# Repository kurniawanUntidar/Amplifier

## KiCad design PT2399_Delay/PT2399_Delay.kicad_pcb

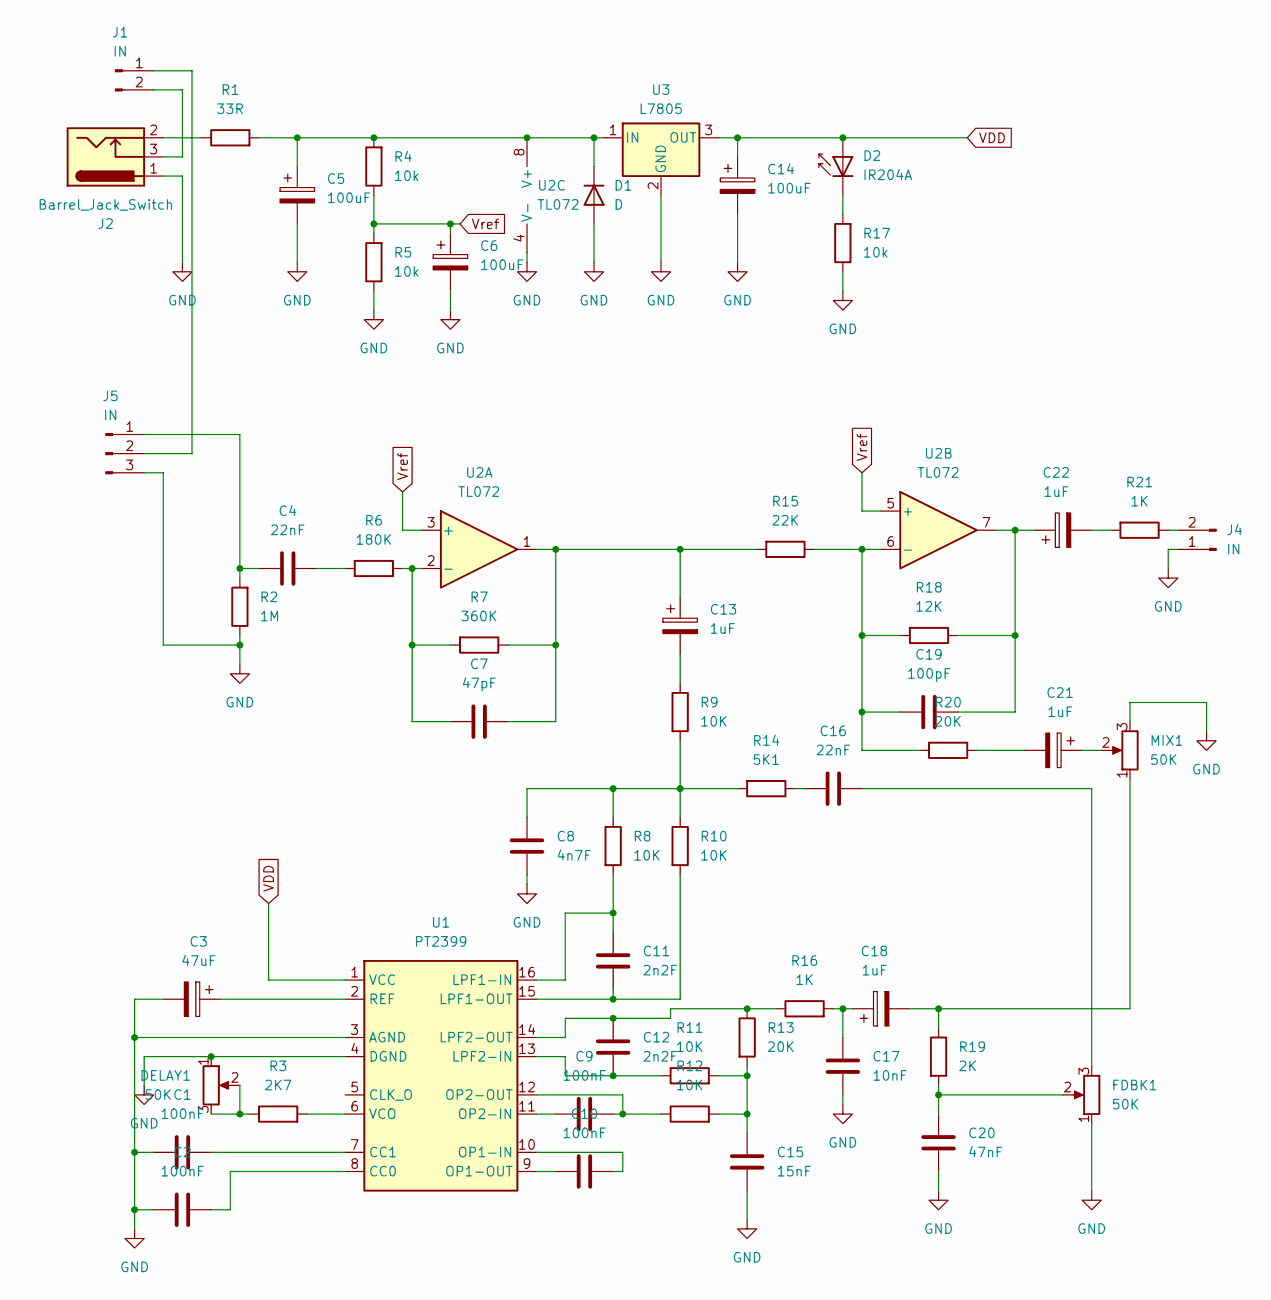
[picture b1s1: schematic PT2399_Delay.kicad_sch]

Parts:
C1, C2, C9, C10: 100nF; C_Axial_L3.8mm_D2.6mm_P7.50mm_Horizontal
C3: 47uF; CP_Radial_D4.0mm_P2.00mm
C4, C16: 22nF; C_Axial_L3.8mm_D2.6mm_P7.50mm_Horizontal
C5, C6, C14: 100uF; CP_Radial_D5.0mm_P2.50mm
C7: 47pF; C_Axial_L3.8mm_D2.6mm_P7.50mm_Horizontal
C8: 4n7F; C_Axial_L3.8mm_D2.6mm_P7.50mm_Horizontal
C11, C12: 2n2F; C_Axial_L3.8mm_D2.6mm_P7.50mm_Horizontal
C13, C18, C21, C22: 1uF; CP_Radial_D4.0mm_P2.00mm
C15: 15nF; C_Axial_L3.8mm_D2.6mm_P7.50mm_Horizontal
C17: 10nF; C_Axial_L3.8mm_D2.6mm_P7.50mm_Horizontal
C19: 100pF; C_Axial_L3.8mm_D2.6mm_P7.50mm_Horizontal
C20: 47nF; C_Axial_L3.8mm_D2.6mm_P7.50mm_Horizontal
D1: D; D_SMC-RM10_Universal_Handsoldering
D2: IR204A; LED_D3.0mm_IRBlack
DELAY1: 50K; Potentiometer_Omeg_PC16BU_Vertical
FDBK1: 50K; Potentiometer_Omeg_PC16BU_Vertical
J1, J4: IN; JST_XA_B02B-XASK-1_1x02_P2.50mm_Vertical
J2: Barrel_Jack_Switch; BarrelJack_GCT_DCJ200-10-A_Horizontal
J5: IN; JST_XA_B03B-XASK-1-A_1x03_P2.50mm_Vertical
MIX1: 50K; Potentiometer_Omeg_PC16BU_Vertical
R1: 33R; R_Axial_DIN0204_L3.6mm_D1.6mm_P5.08mm_Horizontal
R2: 1M; R_Axial_DIN0204_L3.6mm_D1.6mm_P5.08mm_Horizontal
R3: 2K7; R_Axial_DIN0204_L3.6mm_D1.6mm_P5.08mm_Horizontal
R4, R5, R17: 10k; R_Axial_DIN0204_L3.6mm_D1.6mm_P5.08mm_Horizontal
R6: 180K; R_Axial_DIN0204_L3.6mm_D1.6mm_P5.08mm_Horizontal
R7: 360K; R_Axial_DIN0204_L3.6mm_D1.6mm_P5.08mm_Horizontal
R8, R9, R10, R11, R12: 10K; R_Axial_DIN0204_L3.6mm_D1.6mm_P5.08mm_Horizontal
R13, R20: 20K; R_Axial_DIN0204_L3.6mm_D1.6mm_P5.08mm_Horizontal
R14: 5K1; R_Axial_DIN0204_L3.6mm_D1.6mm_P5.08mm_Horizontal
R15: 22K; R_Axial_DIN0204_L3.6mm_D1.6mm_P5.08mm_Horizontal
R16, R21: 1K; R_Axial_DIN0204_L3.6mm_D1.6mm_P5.08mm_Horizontal
R18: 12K; R_Axial_DIN0204_L3.6mm_D1.6mm_P5.08mm_Horizontal
R19: 2K; R_Axial_DIN0204_L3.6mm_D1.6mm_P5.08mm_Horizontal
U1: PT2399; DIP-16_W7.62mm
U2: TL072; DIP-8_W7.62mm
U3: L7805; TO-220F-3_Horizontal_TabUp

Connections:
GND: C1.2, C2.2, C3.2, C5.2, C6.2, C8.1, C14.2, C15.1, C17.1, C20.1, D1.2 (A), DELAY1.1, FDBK1.1, J2.1, J4.1, J5.3, MIX1.3, R2.1, R5.1, R17.1, U1.3 (AGND), U1.4 (DGND), U2.4 (V-), U3.2 (GND)
unnamed: C4.2, R6.2
unnamed: C8.2, R8.1, R9.2, R10.1, R14.2
unnamed: C7.2, C13.1, R7.1, R15.2, U2.1
unnamed: C13.2, R9.1
unnamed: C15.2, R11.2, R12.2, R13.2
unnamed: C16.1, FDBK1.3
unnamed: C16.2, R14.1
unnamed: C17.2, C18.1, R16.2
unnamed: C18.2, MIX1.1, R19.1
unnamed: C19.2, C22.1, R18.1, U2.7
unnamed: C20.2, FDBK1.2, R19.2
unnamed: C21.1, MIX1.2
unnamed: C21.2, R20.1
unnamed: C22.2, R21.2
unnamed: C5.1, D1.1 (K), R1.2, R4.2, U2.8 (V+), U3.1 (IN)
unnamed: D2.1 (K), R17.2
unnamed: DELAY1.2, DELAY1.3, R3.1
unnamed: J1.1, J5.2
unnamed: J1.2, J2.3
unnamed: J2.2, R1.1
unnamed: J4.2, R21.1
unnamed: C4.1, J5.1, R2.2
unnamed: C2.1, U1.8 (CC0)
unnamed: C1.1, U1.7 (CC1)
unnamed: C11.2, R8.2, U1.16 (LPF1-IN)
unnamed: C11.1, R10.2, U1.15 (LPF1-OUT)
unnamed: C12.1, R11.1, U1.13 (LPF2-IN)
unnamed: C12.2, R13.1, R16.1, U1.14 (LPF2-OUT)
unnamed: C10.1, U1.10 (OP1-IN)
unnamed: C10.2, U1.9 (OP1-OUT)
unnamed: C9.2, U1.11 (OP2-IN)
unnamed: C9.1, R12.1, U1.12 (OP2-OUT)
unnamed: C3.1, U1.2 (REF)
unnamed: R3.2, U1.6 (VCO)
unnamed: C7.1, R6.1, R7.2, U2.2 (-)
unnamed: C19.1, R15.1, R18.2, R20.2, U2.6 (-)
VDD: C14.1, D2.2 (A), U1.1 (VCC), U3.3 (OUT)
Vref: C6.1, R4.1, R5.2, U2.3 (+), U2.5 (+)

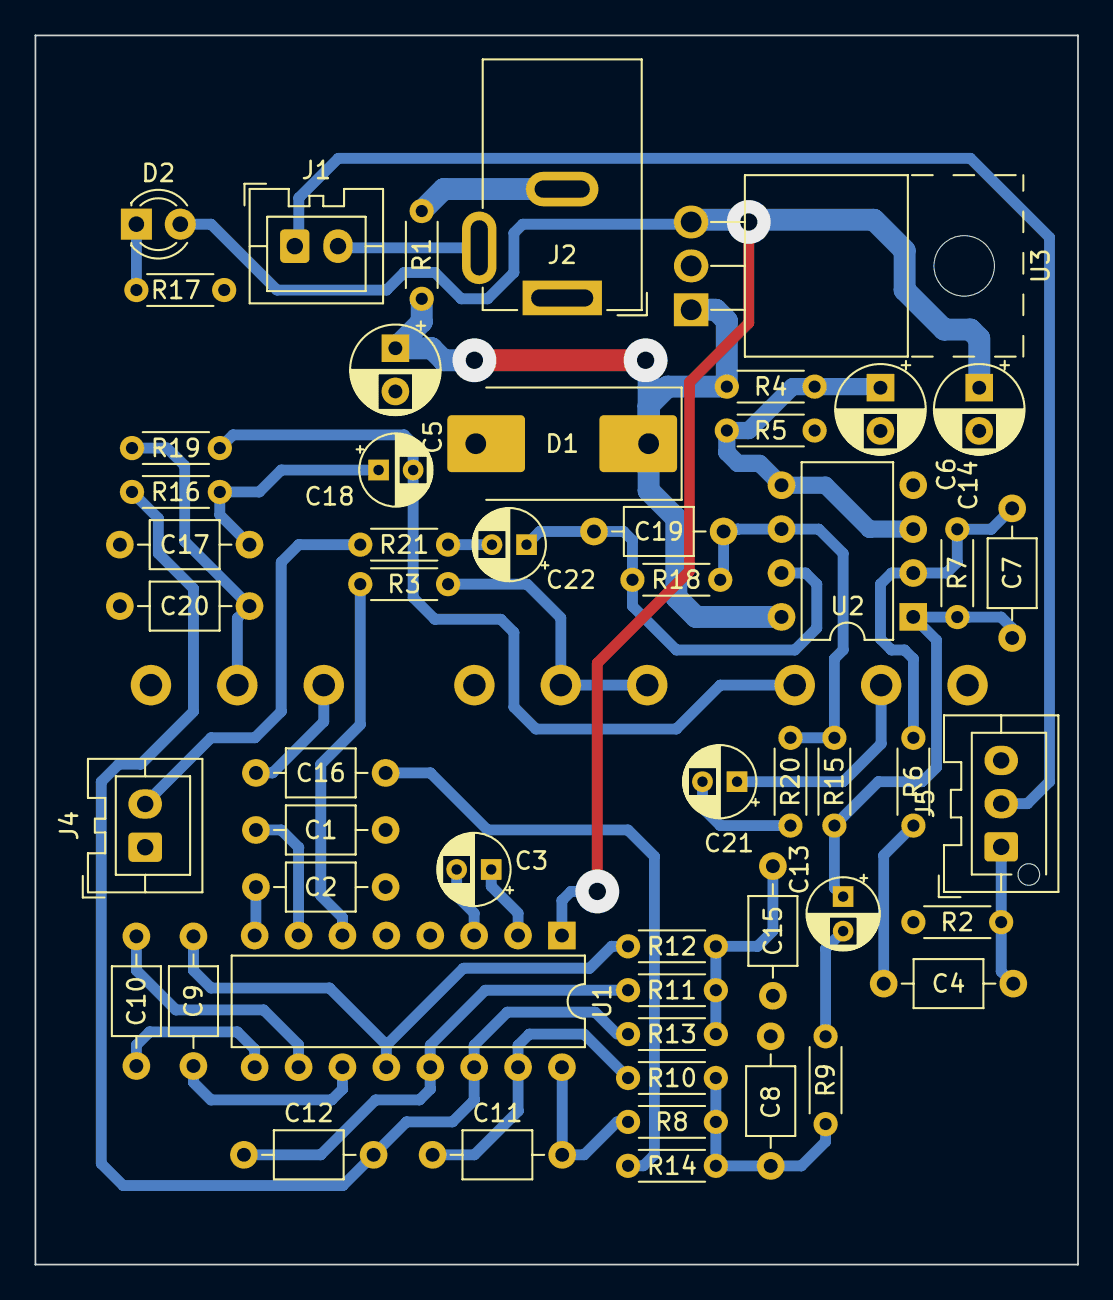
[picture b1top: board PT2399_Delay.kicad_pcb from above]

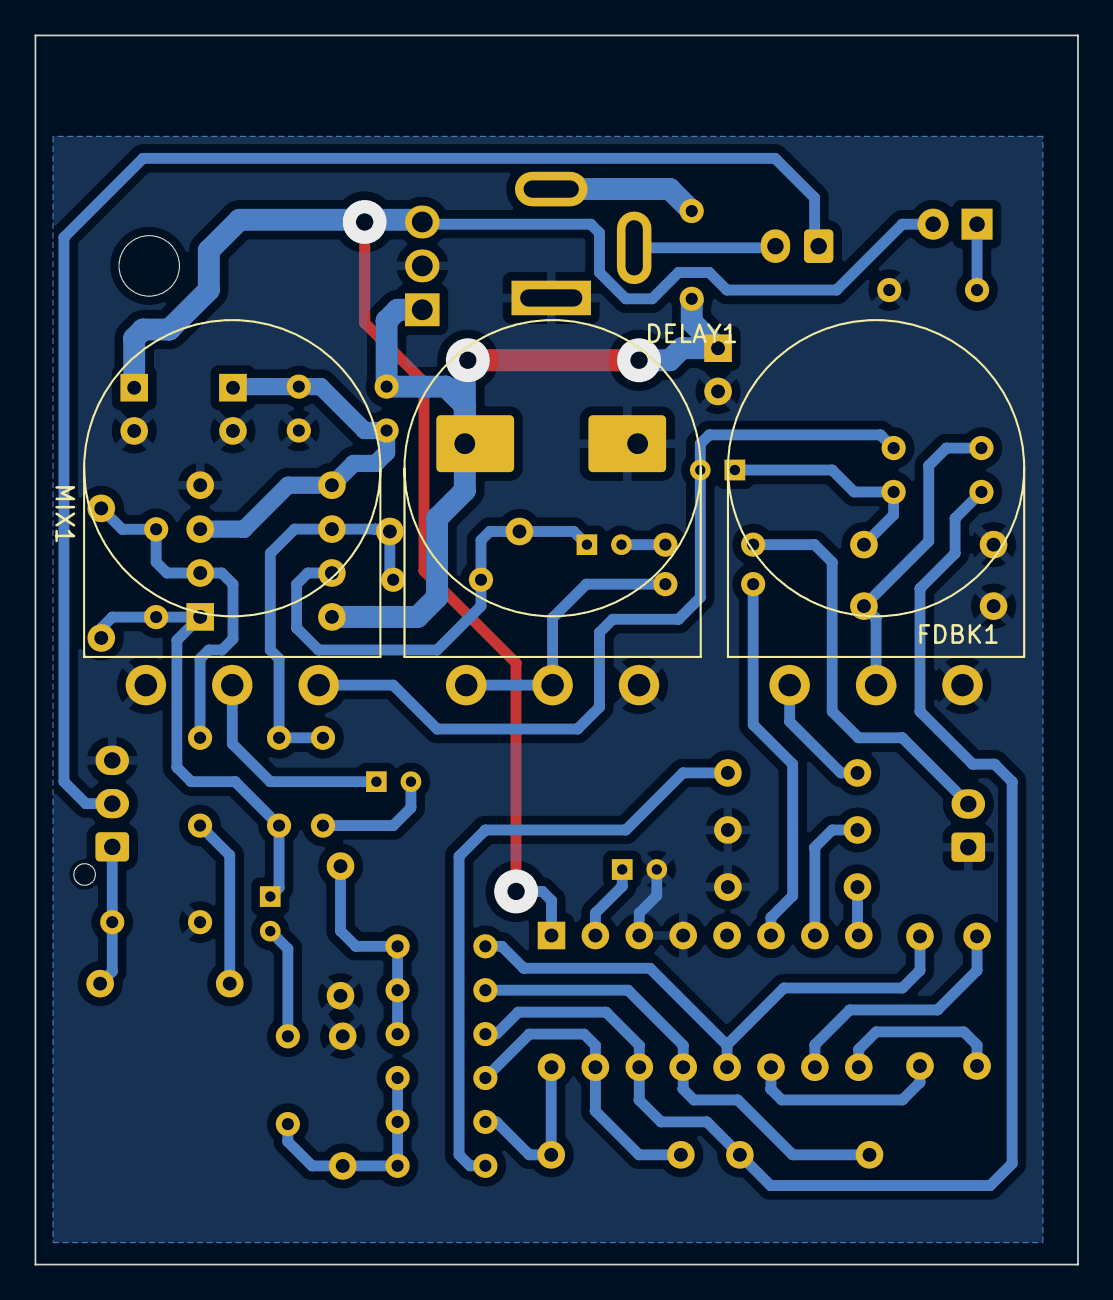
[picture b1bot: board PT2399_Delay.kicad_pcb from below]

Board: 2 copper layers, 60.3 x 71.1 mm, 55 parts (3 on the bottom side), 39 nets.

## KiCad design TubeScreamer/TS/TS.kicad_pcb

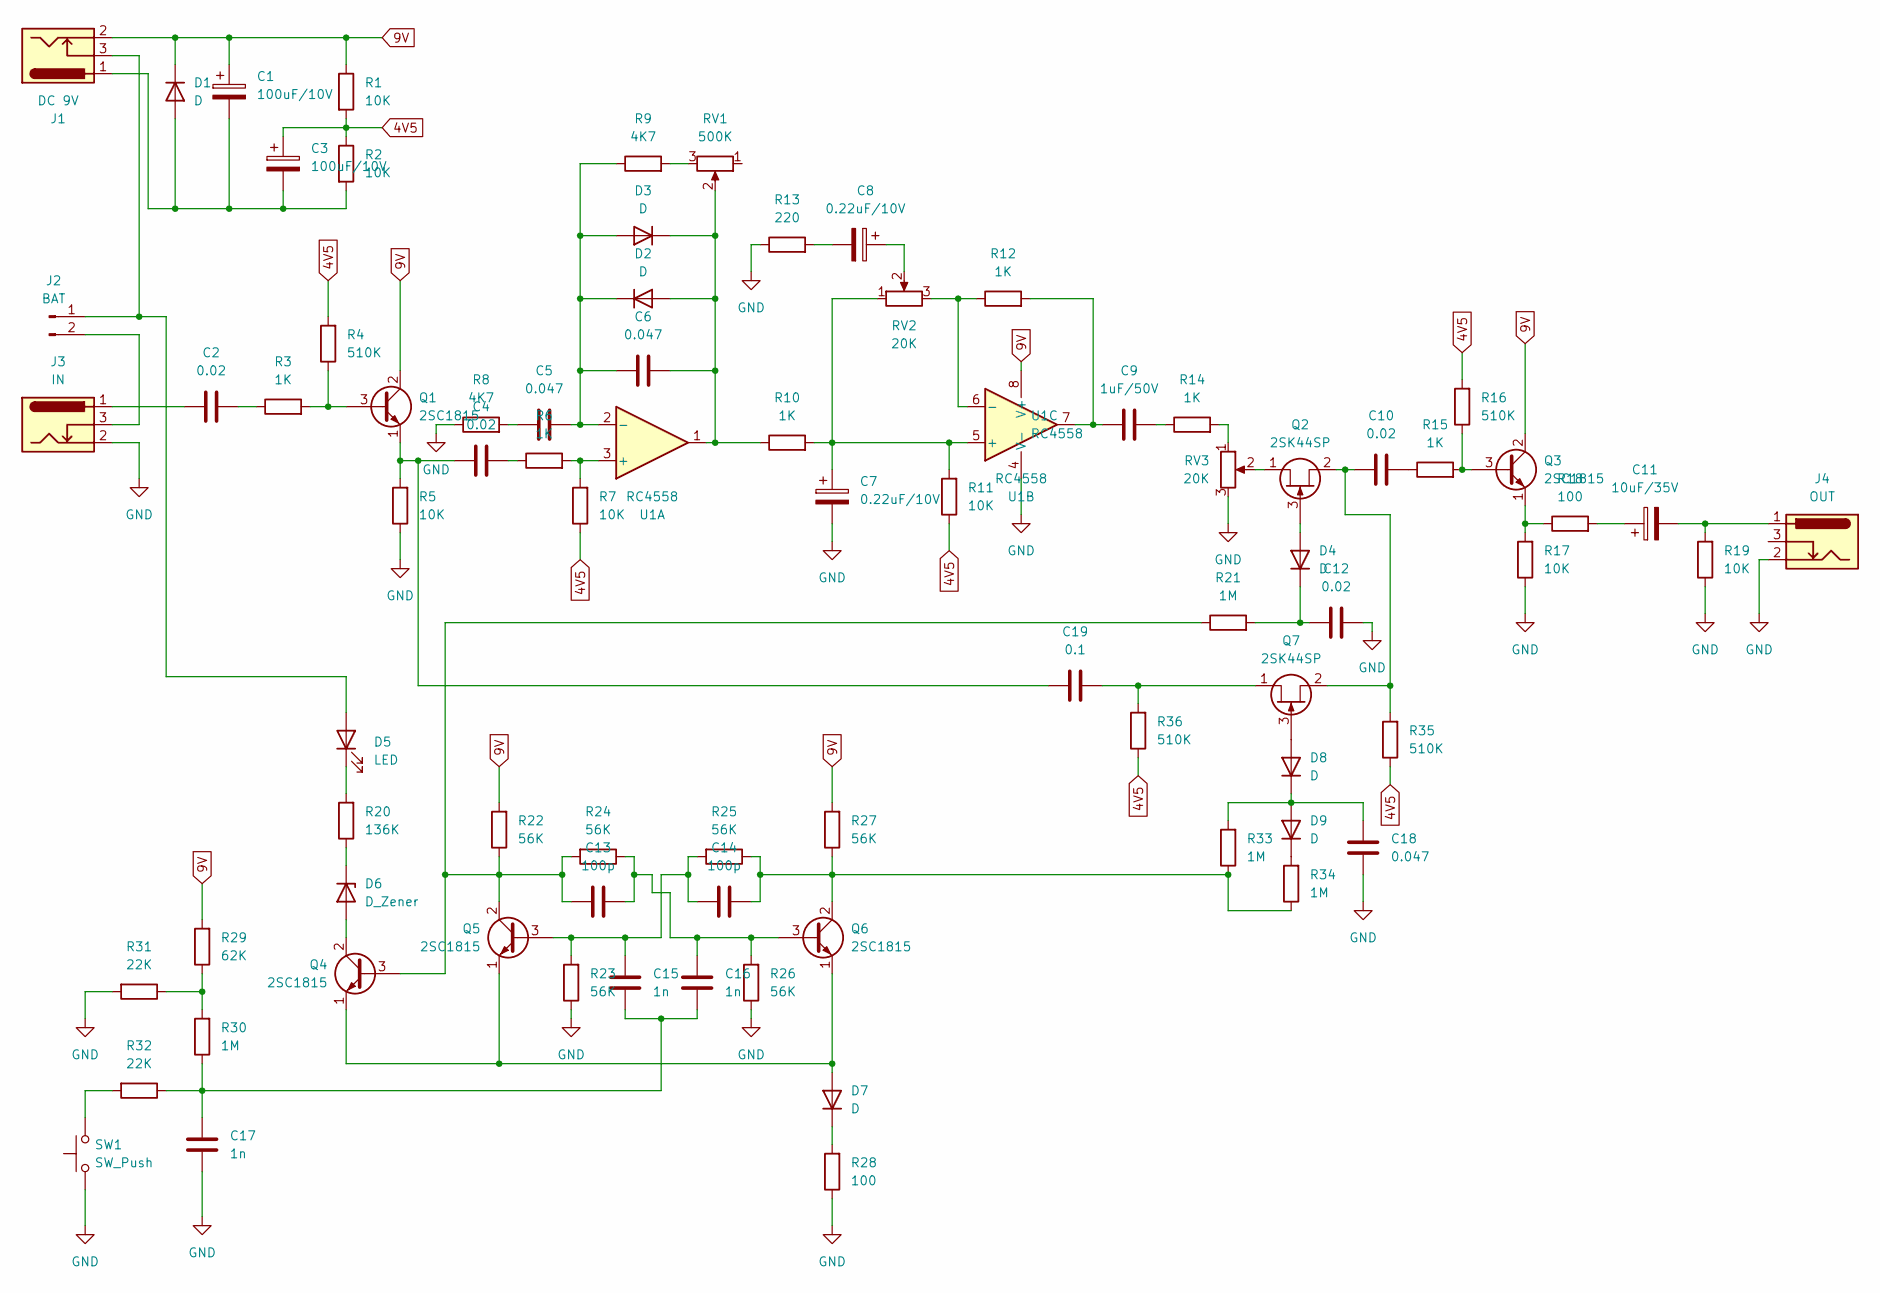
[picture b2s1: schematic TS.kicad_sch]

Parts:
C1, C3: 100uF/10V; CP_Radial_D5.0mm_P2.50mm
C2, C4, C10, C12: 0.02; C_Disc_D4.3mm_W1.9mm_P5.00mm
C5, C6, C18: 0.047; C_Disc_D4.3mm_W1.9mm_P5.00mm
C7, C8: 0.22uF/10V; CP_Radial_D5.0mm_P2.50mm
C9: 1uF/50V; C_Disc_D4.3mm_W1.9mm_P5.00mm
C11: 10uF/35V; CP_Radial_D5.0mm_P2.50mm
C13, C14: 100p; C_Disc_D4.3mm_W1.9mm_P5.00mm
C15, C16, C17: 1n; C_Disc_D4.3mm_W1.9mm_P5.00mm
C19: 0.1; C_Disc_D4.3mm_W1.9mm_P5.00mm
D1, D2, D3, D4, D7, D8, D9: D; D_A-405_P7.62mm_Horizontal
D5: LED; LED_D3.0mm
D6: D_Zener; D_DO-35_SOD27_P7.62mm_Horizontal
J1: DC 9V; BarrelJack_Wuerth_6941xx301002
J2: BAT; PinHeader_1x02_P2.54mm_Vertical
J3: IN; PinHeader_1x03_P2.54mm_Vertical
J4: OUT; PinHeader_1x03_P2.54mm_Vertical
Q1, Q3, Q4, Q5, Q6: 2SC1815; TO-92_Inline
Q2, Q7: 2SK44SP; TO-92L_Inline
R1, R2, R5, R7, R11, R17, R19: 10K; R_Axial_DIN0207_L6.3mm_D2.5mm_P7.62mm_Horizontal
R3, R6, R10, R12, R14, R15: 1K; R_Axial_DIN0207_L6.3mm_D2.5mm_P7.62mm_Horizontal
R4, R16, R35, R36: 510K; R_Axial_DIN0207_L6.3mm_D2.5mm_P7.62mm_Horizontal
R8, R9: 4K7; R_Axial_DIN0207_L6.3mm_D2.5mm_P7.62mm_Horizontal
R13: 220; R_Axial_DIN0207_L6.3mm_D2.5mm_P7.62mm_Horizontal
R18, R28: 100; R_Axial_DIN0207_L6.3mm_D2.5mm_P7.62mm_Horizontal
R20: 136K; R_Axial_DIN0207_L6.3mm_D2.5mm_P7.62mm_Horizontal
R21, R30, R33, R34: 1M; R_Axial_DIN0207_L6.3mm_D2.5mm_P7.62mm_Horizontal
R22, R23, R24, R25, R26, R27: 56K; R_Axial_DIN0207_L6.3mm_D2.5mm_P7.62mm_Horizontal
R29: 62K; R_Axial_DIN0207_L6.3mm_D2.5mm_P7.62mm_Horizontal
R31, R32: 22K; R_Axial_DIN0207_L6.3mm_D2.5mm_P7.62mm_Horizontal
RV1: 500K; PinHeader_1x03_P2.54mm_Vertical
RV2, RV3: 20K; PinHeader_1x03_P2.54mm_Vertical
SW1: SW_Push; PinHeader_1x02_P2.54mm_Vertical
U1: RC4558; DIP-8_W7.62mm_Socket

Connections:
4V5: C3.1, R1.2, R2.1, R4.2, R7.1, R11.1, R16.2, R35.1, R36.1
9V: C1.1, D1.1 (K), J1.2, Q1.2 (C), Q3.2 (C), R1.1, R22.2, R27.2, R29.2, U1.8 (V+)
GND: C7.2, C12.2, C17.1, C18.1, J3.2, J4.2, R5.1, R8.1, R13.1, R17.1, R19.1, R23.1, R26.1, R28.1, R31.2, RV3.3, SW1.1, U1.4 (V-)
unnamed: C2.1, J3.1
unnamed: C2.2, R3.1
unnamed: C4.2, R6.1
unnamed: C5.1, R8.2
unnamed: C8.1, RV2.2
unnamed: C8.2, R13.2
unnamed: C9.1, R12.2, U1.7
unnamed: C9.2, R14.1
unnamed: C10.2, R15.1
unnamed: C11.1, R18.2
unnamed: C11.2, J4.1, R19.2
unnamed: C15.1, C16.1, C17.2, R30.1, R32.1
unnamed: C1.2, C3.2, D1.2 (A), J1.1, R2.2
unnamed: C6.2, D2.2 (A), D3.1 (K), R10.1, RV1.2, U1.1
unnamed: C5.2, C6.1, D2.1 (K), D3.2 (A), R9.1, U1.2 (-)
unnamed: D4.2 (A), Q2.3 (G)
unnamed: C12.1, D4.1 (K), R21.2
unnamed: D5.2 (A), J1.3, J2.1
unnamed: D5.1 (K), R20.2
unnamed: D6.2 (A), Q4.2 (C)
unnamed: D6.1 (K), R20.1
unnamed: D7.2 (A), Q4.1 (E), Q5.1 (E), Q6.1 (E)
unnamed: D7.1 (K), R28.2
unnamed: D8.2 (A), Q7.3 (G)
unnamed: C18.2, D8.1 (K), D9.2 (A), R33.2
unnamed: D9.1 (K), R34.2
unnamed: J2.2, J3.3
unnamed: Q1.3 (B), R3.2, R4.1
unnamed: C4.1, C19.1, Q1.1 (E), R5.2
unnamed: Q2.1 (D), RV3.2
unnamed: C10.1, Q2.2 (S), Q7.2 (S), R35.2
unnamed: Q3.3 (B), R15.2, R16.1
unnamed: Q3.1 (E), R17.2, R18.1
unnamed: C13.1, Q4.3 (B), Q5.2 (C), R21.1, R22.1, R24.2
unnamed: C14.1, C15.2, Q5.3 (B), R23.2, R25.2
unnamed: C13.2, C16.2, Q6.3 (B), R24.1, R26.2
unnamed: C14.2, Q6.2 (C), R25.1, R27.1, R33.1, R34.1
unnamed: C19.2, Q7.1 (D), R36.2
unnamed: R9.2, RV1.3
unnamed: R14.2, RV3.1
unnamed: R29.1, R30.2, R31.1
unnamed: R32.2, SW1.2
unnamed: R6.2, R7.2, U1.3 (+)
unnamed: C7.1, R10.2, R11.2, RV2.1, U1.5 (+)
unnamed: R12.1, RV2.3, U1.6 (-)

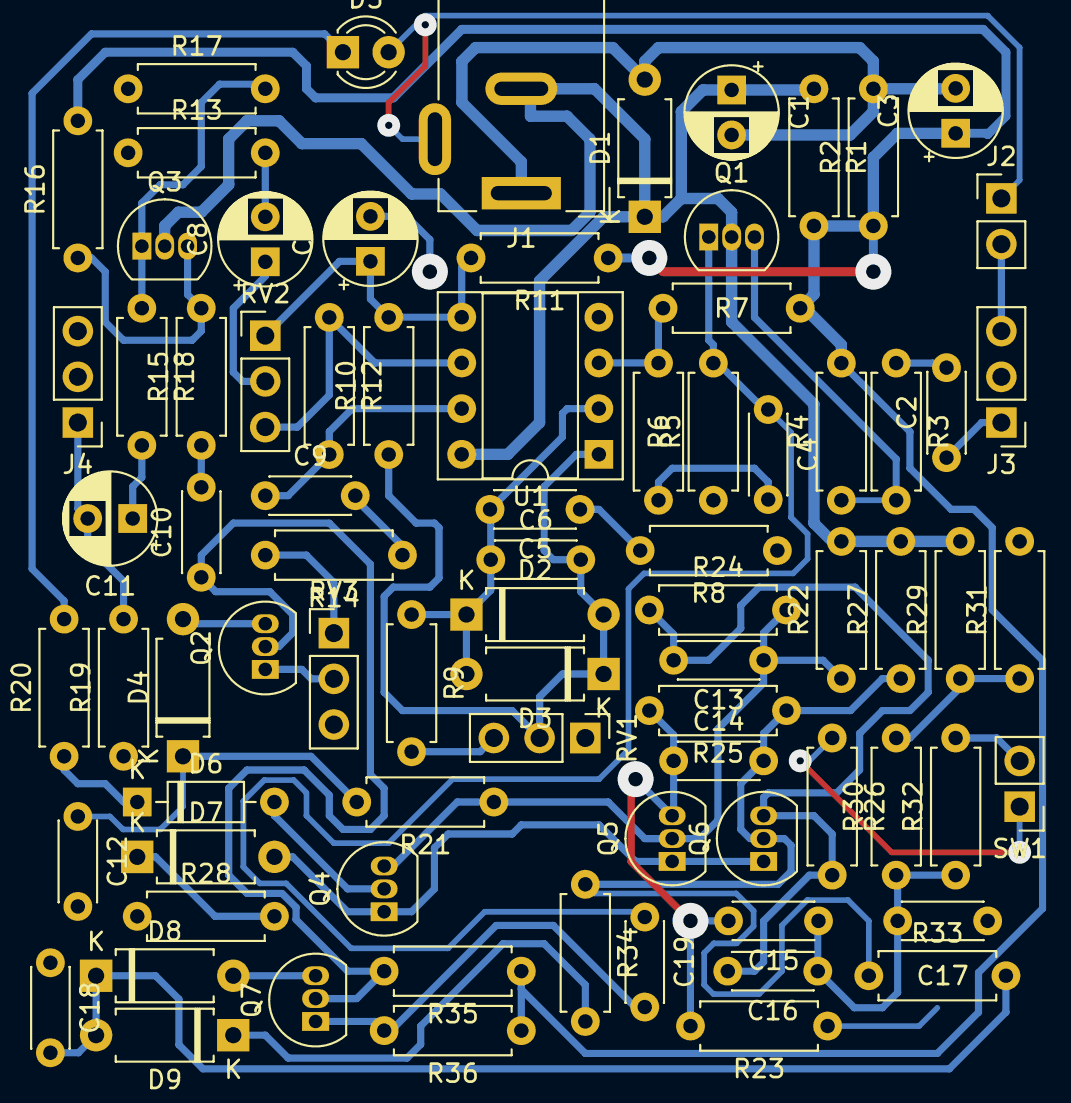
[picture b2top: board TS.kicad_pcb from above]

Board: 2 copper layers, 80 parts (0 on the bottom side), 48 nets.

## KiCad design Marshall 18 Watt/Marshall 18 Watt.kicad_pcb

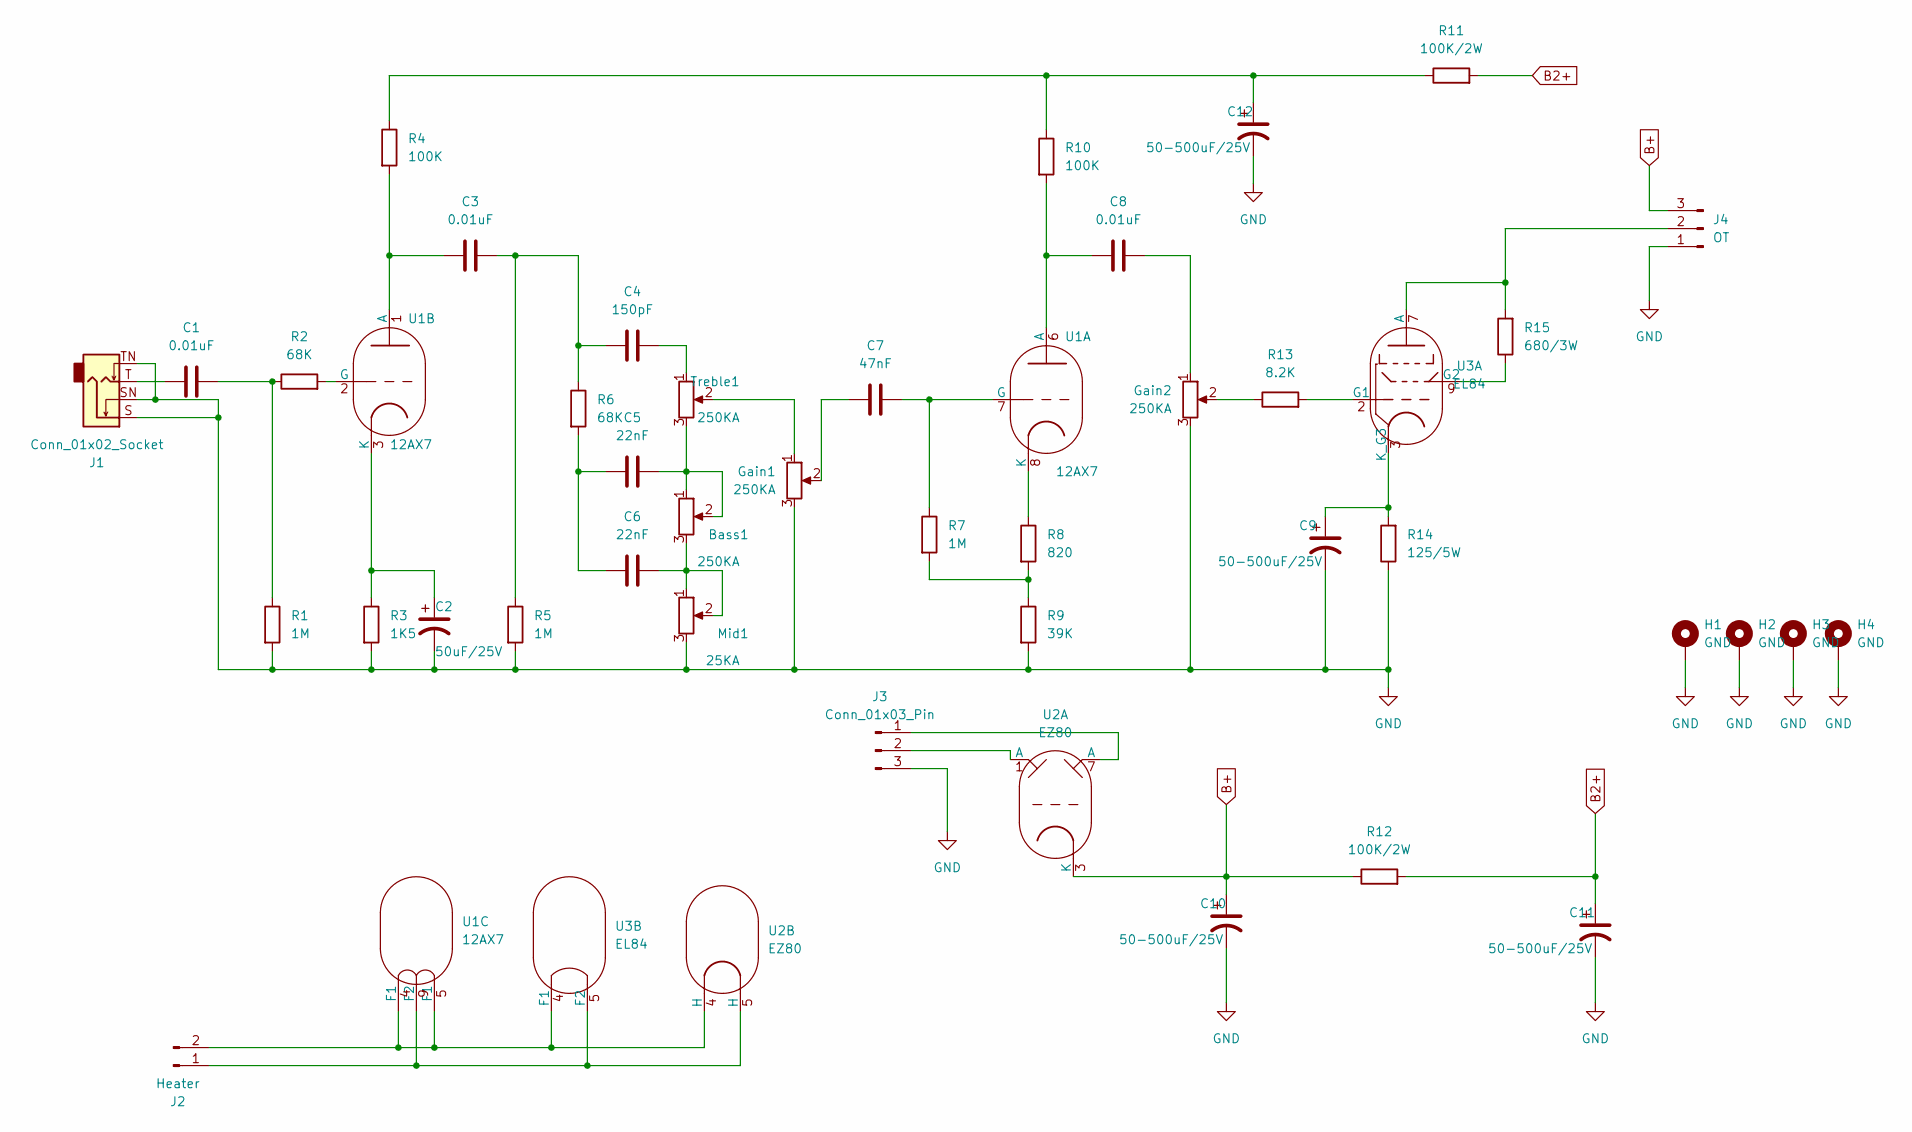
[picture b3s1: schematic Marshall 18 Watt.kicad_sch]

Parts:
Bass1: 250KA; Potentiometer_Alps_RK163_Single_Horizontal
C1, C3, C8: 0.01uF; C_Rect_L29.0mm_W7.6mm_P27.50mm_MKT
C2: 50uF/25V; CP_Radial_D10.0mm_P3.80mm
C4: 150pF; C_Rect_L29.0mm_W7.6mm_P27.50mm_MKT
C5, C6: 22nF; C_Rect_L29.0mm_W7.6mm_P27.50mm_MKT
C7: 47nF; C_Rect_L29.0mm_W7.6mm_P27.50mm_MKT
C9: 50-500uF/25V; CP_Radial_D10.0mm_P3.80mm
C10, C11, C12: 50-500uF/25V; CP_Radial_D18.0mm_P7.50mm
Gain1, Gain2: 250KA; Potentiometer_Alps_RK163_Single_Horizontal
H1, H2, H3, H4: GND; MountingHole_2.5mm_Pad_TopBottom
J1: Conn_01x02_Socket; Jack_6.35mm_Neutrik_NMJ4HCD2_Horizontal
J2: Heater; PhoenixContact_MCV_1,5_2-G-5.08_1x02_P5.08mm_Vertical
J3: Conn_01x03_Pin; PhoenixContact_MCV_1,5_3-G-5.08_1x03_P5.08mm_Vertical
J4: OT; PhoenixContact_MCV_1,5_3-G-5.08_1x03_P5.08mm_Vertical
Mid1: 25KA; Potentiometer_Alps_RK163_Single_Horizontal
R1, R5, R7: 1M; R_Axial_DIN0411_L9.9mm_D3.6mm_P20.32mm_Horizontal
R2, R6: 68K; R_Axial_DIN0411_L9.9mm_D3.6mm_P20.32mm_Horizontal
R3: 1K5; R_Axial_DIN0411_L9.9mm_D3.6mm_P20.32mm_Horizontal
R4, R10: 100K; R_Axial_DIN0411_L9.9mm_D3.6mm_P20.32mm_Horizontal
R8: 820; R_Axial_DIN0411_L9.9mm_D3.6mm_P20.32mm_Horizontal
R9: 39K; R_Axial_DIN0411_L9.9mm_D3.6mm_P20.32mm_Horizontal
R11, R12: 100K/2W; R_Axial_DIN0411_L9.9mm_D3.6mm_P20.32mm_Horizontal
R13: 8.2K; R_Axial_DIN0411_L9.9mm_D3.6mm_P20.32mm_Horizontal
R14: 125/5W; R_Axial_DIN0411_L9.9mm_D3.6mm_P20.32mm_Horizontal
R15: 680/3W; R_Axial_DIN0411_L9.9mm_D3.6mm_P20.32mm_Horizontal
Treble1: 250KA; Potentiometer_Alps_RK163_Single_Horizontal
U1: 12AX7; 9P_2.57mm
U2: EZ80; 9P_2.57mm
U3: EL84; 9P_2.57mm

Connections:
B2+: C11.1, R11.2, R12.2
B+: C10.1, J4.3, R12.1, U2.3 (K)
GND: C2.2, C9.2, C10.2, C11.2, C12.2, Gain1.3, Gain2.3, H1.1, H2.1, H3.1, H4.1, J1.S, J1.SN, J1.TN, J3.3, J4.1, Mid1.3, R1.2, R3.2, R5.2, R9.2, R14.1
unnamed: Bass1.1, Bass1.2, C5.2, Treble1.3
unnamed: Bass1.3, C6.2, Mid1.1, Mid1.2
unnamed: C1.1, J1.T
unnamed: C1.2, R1.1, R2.1
unnamed: C3.2, C4.1, R5.1, R6.1
unnamed: C4.2, Treble1.1
unnamed: C5.1, C6.1, R6.2
unnamed: C7.1, Gain1.2
unnamed: C8.2, Gain2.1
unnamed: C12.1, R4.1, R10.1, R11.1
unnamed: Gain1.1, Treble1.2
unnamed: Gain2.2, R13.1
unnamed: J2.1, U1.9 (F2), U2.5 (H), U3.5 (F2)
unnamed: J2.2, U1.4 (F1), U1.5 (F1), U2.4 (H), U3.4 (F1)
unnamed: J3.1, U2.7 (A)
unnamed: J3.2, U2.1 (A)
unnamed: J4.2, R15.2, U3.7 (A)
unnamed: R7.2, R8.2, R9.1
unnamed: C8.1, R10.2, U1.6 (A)
unnamed: C7.2, R7.1, U1.7 (G)
unnamed: R8.1, U1.8 (K)
unnamed: C3.1, R4.2, U1.1 (A)
unnamed: R2.2, U1.2 (G)
unnamed: C2.1, R3.1, U1.3 (K)
unnamed: R13.2, U3.2 (G1)
unnamed: R15.1, U3.9 (G2)
unnamed: C9.1, R14.2, U3.3 (K_G3)

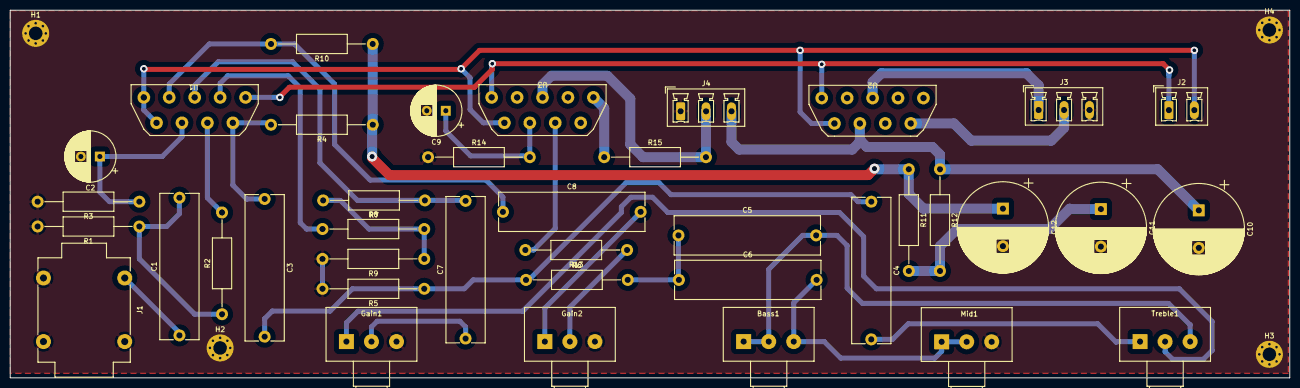
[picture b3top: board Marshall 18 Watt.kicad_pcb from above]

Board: 2 copper layers, 255.5 x 73.4 mm, 43 parts (0 on the bottom side), 30 nets.

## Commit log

2024-12-15 update
    first
2025-03-11 Update 11_03_25
    add fender champ
2025-03-16 Update_17_03_25
    Add sch
2025-03-17 update 17_03_25
    add lib
2025-03-17 bdhdf
    xgsdgsdgs
2025-03-18 Update 18_03_25
    V01
2025-03-26 Update_26_03_25
    Add Delay
2025-03-26 update_26_03_25
    Rev Delay
2025-03-26 Update _26_03_25
    PCB
2025-03-27 update_27_03_25
    add distortion
2025-03-27 Update 27_03_25
    Add TS
2025-03-27 Update 27_03_15
    sch TS fix
